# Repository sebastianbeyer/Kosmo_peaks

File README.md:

# Summit is a KOSMO adaption of [Matias Levy's bluepill version](https://github.com/matias-levy/peaks) of [Mutable instrument's Peaks](https://mutable-instruments.net/modules/peaks/)

> **Warning**
> You need the 128k flash version of the bluepill board which might be difficult to obtain. I was lucky with [this](https://www.amazon.com/Teyleten-Robot-Development-STM32F103C8T6-Learning/dp/B08THXZ6XK) item, someone on the LMNC forum was able to get a 128k [here on aliexpress](https://www.aliexpress.us/item/3256801435312142.html?spm=a2g0o.order_list.0.0.4e301802nbwQXK&gatewayAdapt=glo2usa&_randl_shipto=US), but there is no guarantee!

## Gerbers
Can be found in the [latest release](https://github.com/sebastianbeyer/Kosmo_peaks/releases/latest)

## Firmwares
There's the option to flash one of two firmwares that where ported. The original Mutable Instruments one is in the firmware/peaks directory. The [Mutated Mutables Dead Man's Catch](https://github.com/timchurches/Mutated-Mutables/tree/master/peaks) is in the firmware/peaks2. The later adds a lot of functionality to the module, although the UI becomes a bit confusing. <br>
Compiled binaries and HEX files are provided for both under firmware/build.

## Changes
* Added a driver for the PWM DAC running at **14 bit depth, 48Khz sampling rate.** (File in firmware/peaks/drivers/pwm_dac.h)
* Activated the clock for the TIM4 in firmware/peaks/drivers/system.cc
* **Bypassed the bootloader:** This was done as to simplify the code, it does not interfere with the calibration functionality of the module.
* Redesigned the output portion of the hardware to accommodate to the PWM levels.

## Flashing and development
To make it easier I have left binaries and .HEX files in firmware/build, this can be flashed directly to the bluepill using [STM32CubeProgrammer](https://www.st.com/en/development-tools/stm32cubeprog.html). <br>
Another option is to install the [mutable-dev-environment](https://github.com/pichenettes/mutable-dev-environment) and replace the peaks folder with the one inside /firmware, then executing

    make -f peaks/makefile upload_serial

We use this command because the bootloader is bypassed.

## Thanks
I want to thank Emilie Gillet for open-sourcing her work which is a constant inspiration for many musicians and makers, and encourage everyone interested in this project to checkout the [Mutable instrument's Forum](https://forum.mutable-instruments.net/) in which Emilie is a very active member.

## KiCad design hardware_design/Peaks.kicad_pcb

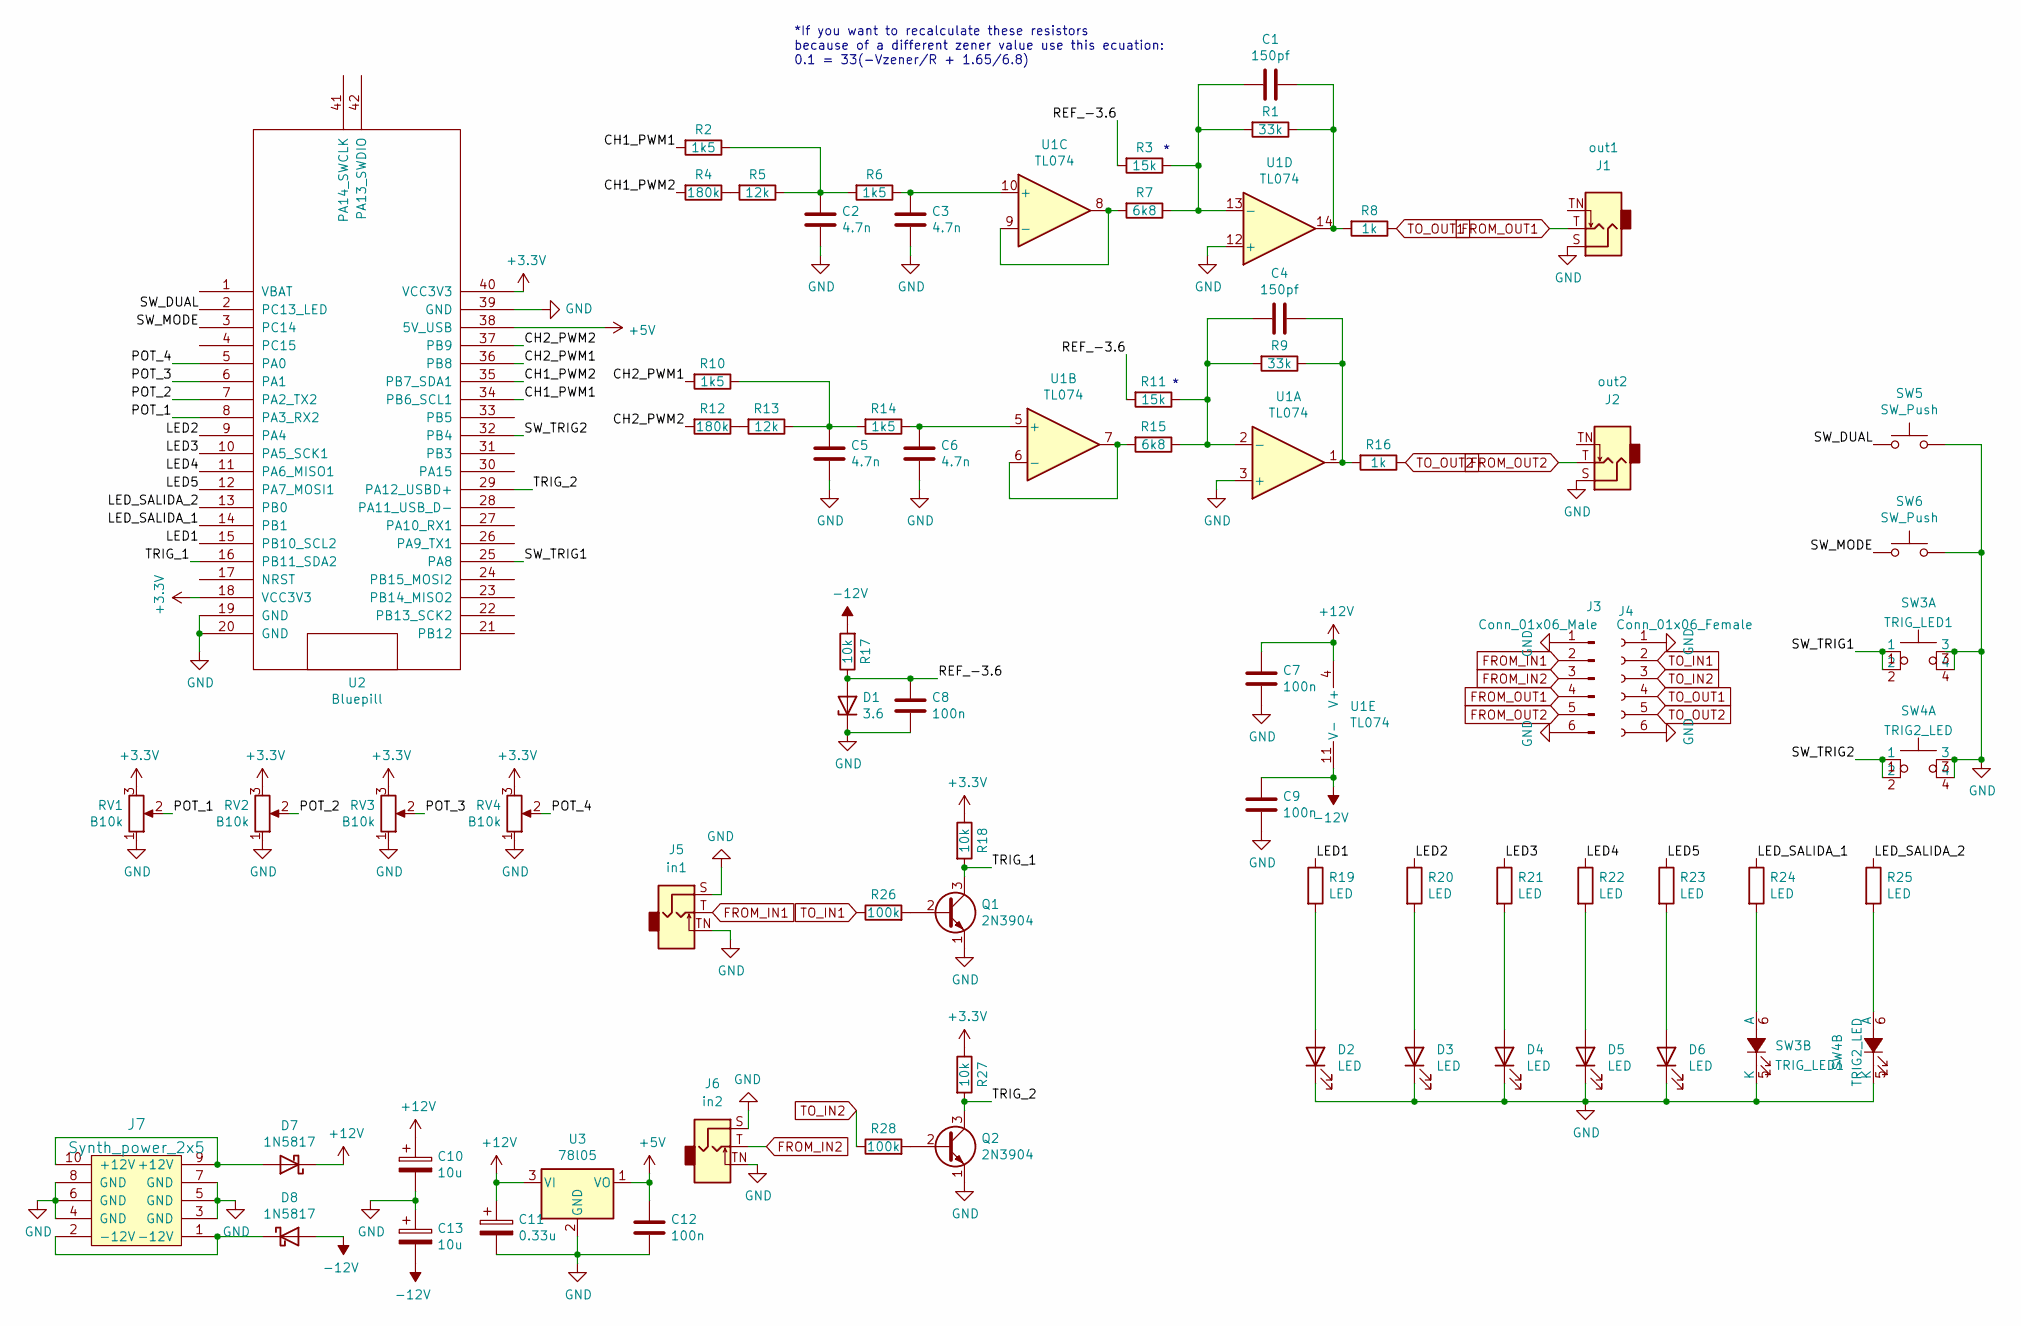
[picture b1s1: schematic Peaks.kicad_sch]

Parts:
C1, C4: 150pf; C_Disc_D3.0mm_W1.6mm_P2.50mm
C2, C3, C5, C6: 4.7n; C_Disc_D3.0mm_W1.6mm_P2.50mm
C7, C8, C9, C12: 100n; C_Disc_D3.0mm_W1.6mm_P2.50mm
C10, C13: 10u; CP_Radial_horizontalflat_D5mm_P2.50mm_H10mm_south
C11: 0.33u; CP_Radial_horizontalflat_D5mm_P2.50mm_H10mm_south
D1: 3.6; D_DO-35_SOD27_P7.62mm_Horizontal
D2, D3, D4, D5, D6: LED; LED_D3.0mm_FlatTop
D7, D8: 1N5817; D_DO-41_SOD81_P10.16mm_Horizontal
J1: out1; Jack_6.35mm_PJ_629HAN_slots
J2: out2; Jack_6.35mm_PJ_629HAN_slots
J3: Conn_01x06_Male; PinHeader_1x06_P2.54mm_Vertical
J4: Conn_01x06_Female; PinSocket_1x06_P2.54mm_Vertical
J5: in1; Jack_6.35mm_PJ_629HAN_slots
J6: in2; Jack_6.35mm_PJ_629HAN_slots
J7: Synth_power_2x5; Power_Header
Q1, Q2: 2N3904; TO-92_Inline_Wide
R1, R9: 33k; R_Axial_DIN0207_L6.3mm_D2.5mm_P10.16mm_Horizontal
R2, R6, R10, R14: 1k5; R_Axial_DIN0207_L6.3mm_D2.5mm_P10.16mm_Horizontal
R3, R11: 15k; R_Axial_DIN0207_L6.3mm_D2.5mm_P10.16mm_Horizontal
R4, R12: 180k; R_Axial_DIN0207_L6.3mm_D2.5mm_P10.16mm_Horizontal
R5, R13: 12k; R_Axial_DIN0207_L6.3mm_D2.5mm_P10.16mm_Horizontal
R7, R15: 6k8; R_Axial_DIN0207_L6.3mm_D2.5mm_P10.16mm_Horizontal
R8, R16: 1k; R_Axial_DIN0207_L6.3mm_D2.5mm_P10.16mm_Horizontal
R17: 10k; R_Axial_DIN0207_L6.3mm_D2.5mm_P10.16mm_Horizontal
R18, R27: 10k; R_Axial_DIN0207_L6.3mm_D2.5mm_P2.54mm_Vertical
R19, R20, R21, R22, R23, R24, R25: LED; R_Axial_DIN0207_L6.3mm_D2.5mm_P2.54mm_Vertical
R26, R28: 100k; R_Axial_DIN0207_L6.3mm_D2.5mm_P2.54mm_Vertical
RV1, RV2, RV3, RV4: B10k; Potentiometer_Alpha_RD901F-40-00D_Single_Vertical_centered
SW3: TRIG_LED1; HIGHLY_PB6149L
SW4: TRIG2_LED; HIGHLY_PB6149L
SW5, SW6: SW_Push; SW_PUSH_6mm_H13mm
U1: TL074; DIP-14_W7.62mm_Socket_LongPads
U2: Bluepill; BluePill_STM32F103C
U3: 78l05; TO-220-3_Horizontal_TabDown

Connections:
+3V3: R18.1, R27.1, RV1.3, RV2.3, RV3.3, RV4.3, U2.18 (VCC3V3), U2.40 (VCC3V3)
+5V: C12.1, U2.38 (5V_USB), U3.1 (VO)
+12V: C7.1, C10.1, C11.1, D7.1 (K), U1.4 (V+), U3.3 (VI)
-12V: C9.1, C13.2, D8.2 (A), R17.2, U1.11 (V-)
/CH1_PWM1: R2.2, U2.34 (PB6_SCL1)
/CH1_PWM2: R4.2, U2.35 (PB7_SDA1)
/CH2_PWM1: R10.2, U2.36 (PB8)
/CH2_PWM2: R12.2, U2.37 (PB9)
/LED1: R19.1, U2.15 (PB10_SCL2)
/LED2: R20.1, U2.9 (PA4)
/LED3: R21.1, U2.10 (PA5_SCK1)
/LED4: R22.1, U2.11 (PA6_MISO1)
/LED5: R23.1, U2.12 (PA7_MOSI1)
/LED_SALIDA_1: R24.1, U2.14 (PB1)
/LED_SALIDA_2: R25.1, U2.13 (PB0)
/POT_1: RV1.2, U2.8 (PA3_RX2)
/POT_2: RV2.2, U2.7 (PA2_TX2)
/POT_3: RV3.2, U2.6 (PA1)
/POT_4: RV4.2, U2.5 (PA0)
/REF_-3.6: C8.1, D1.2 (A), R3.2, R11.2, R17.1
/SW_DUAL: SW5.1, U2.2 (PC13_LED)
/SW_MODE: SW6.1, U2.3 (PC14)
/SW_TRIG1: SW3.1, SW3.2, U2.25 (PA8)
/SW_TRIG2: SW4.1, SW4.2, U2.32 (PB4)
/TRIG_1: Q1.3 (C), R18.2, U2.16 (PB11_SDA2)
/TRIG_2: Q2.3 (C), R27.2, U2.29 (PA12_USBD+)
FROM_IN1: J3.2, J5.T
FROM_IN2: J3.3, J6.T
FROM_OUT1: J1.T, J3.4
FROM_OUT2: J2.T, J3.5
GND: C2.2, C3.2, C5.2, C6.2, C7.2, C8.2, C9.2, C10.2, C11.2, C12.2, C13.1, D1.1 (K), D2.1 (K), D3.1 (K), D4.1 (K), D5.1 (K), D6.1 (K), J1.S, J2.S, J3.1, J3.6, J4.1, J4.6, J5.S, J5.TN, J6.S, J6.TN, J7.3 (GND), J7.4 (GND), J7.5 (GND), J7.6 (GND), J7.7 (GND), J7.8 (GND), Q1.1 (E), Q2.1 (E), RV1.1, RV2.1, RV3.1, RV4.1, SW3.3, SW3.4, SW3.5 (K), SW4.3, SW4.4, SW4.5 (K), SW5.2, SW6.2, U1.3 (+), U1.12 (+), U2.19 (GND), U2.20 (GND), U2.39 (GND), U3.2 (GND)
unnamed: C1.1, R1.2, R3.1, R7.1, U1.13 (-)
unnamed: C1.2, R1.1, R8.2, U1.14
unnamed: C2.1, R2.1, R5.1, R6.2
unnamed: C3.1, R6.1, U1.10 (+)
unnamed: C4.1, R9.2, R11.1, R15.1, U1.2 (-)
unnamed: C4.2, R9.1, R16.2, U1.1
unnamed: C5.1, R10.1, R13.1, R14.2
unnamed: C6.1, R14.1, U1.5 (+)
unnamed: D2.2 (A), R19.2
unnamed: D3.2 (A), R20.2
unnamed: D4.2 (A), R21.2
unnamed: D5.2 (A), R22.2
unnamed: D6.2 (A), R23.2
unnamed: D7.2 (A), J7.9 (+12V), J7.10 (+12V)
unnamed: D8.1 (K), J7.1 (-12V), J7.2 (-12V)
unnamed: Q1.2 (B), R26.2
unnamed: Q2.2 (B), R28.2
unnamed: R4.1, R5.2
unnamed: R7.2, U1.8, U1.9 (-)
unnamed: R12.1, R13.2
unnamed: R15.2, U1.6 (-), U1.7
unnamed: R24.2, SW3.6 (A)
unnamed: R25.2, SW4.6 (A)
TO_IN1: J4.2, R26.1
TO_IN2: J4.3, R28.1
TO_OUT1: J4.4, R8.1
TO_OUT2: J4.5, R16.1

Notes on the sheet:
*If you want to recalculate these resistors because of a different zener value use this ecuation: 0.1 = 33(-Vzener/R + 1.65/6.8)

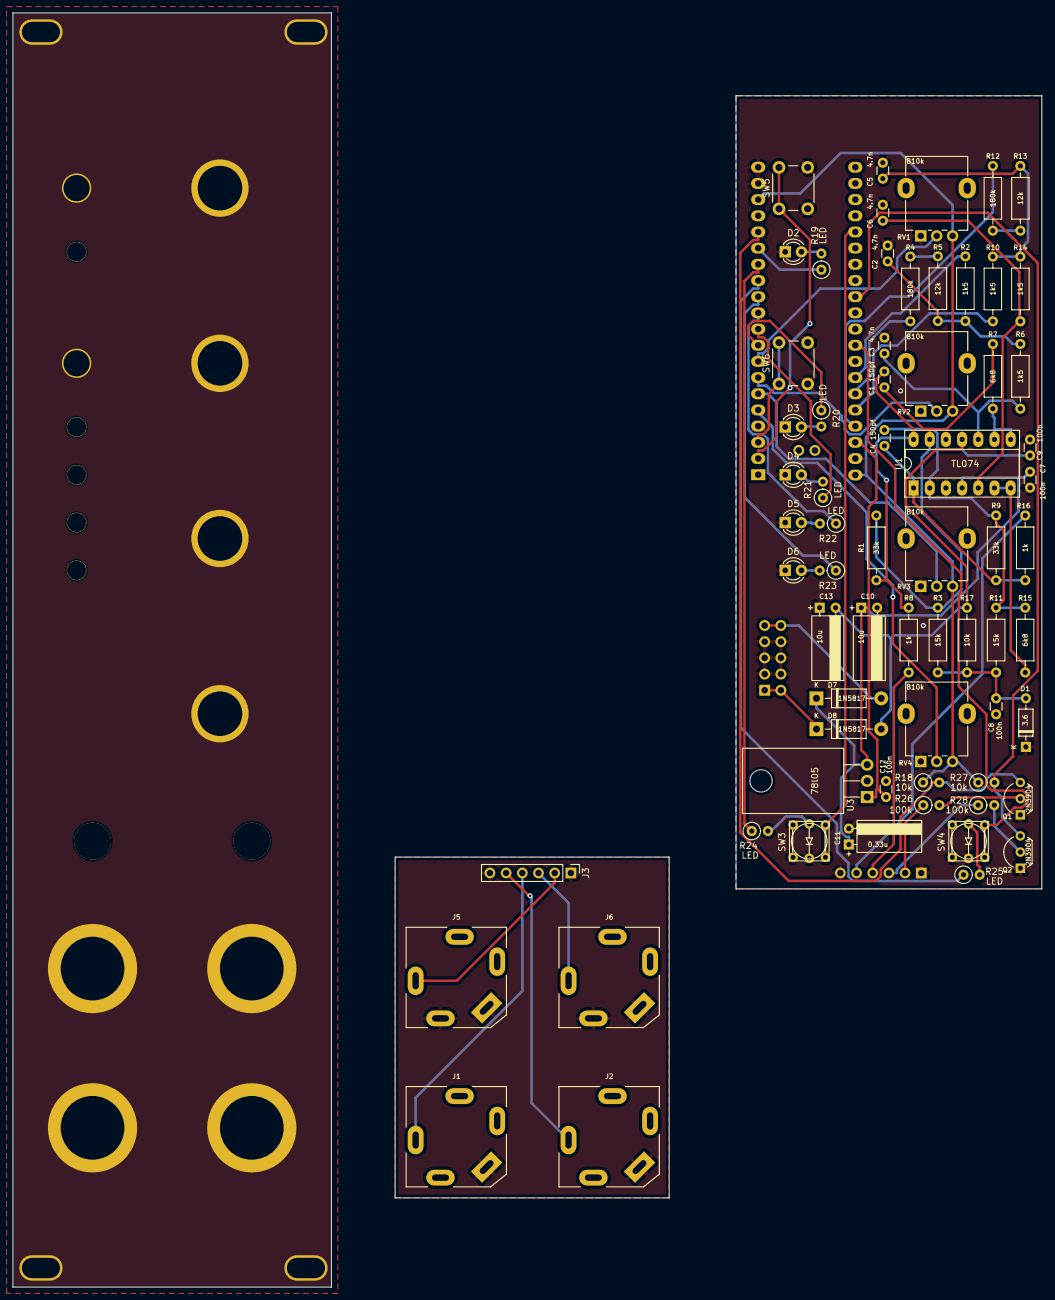
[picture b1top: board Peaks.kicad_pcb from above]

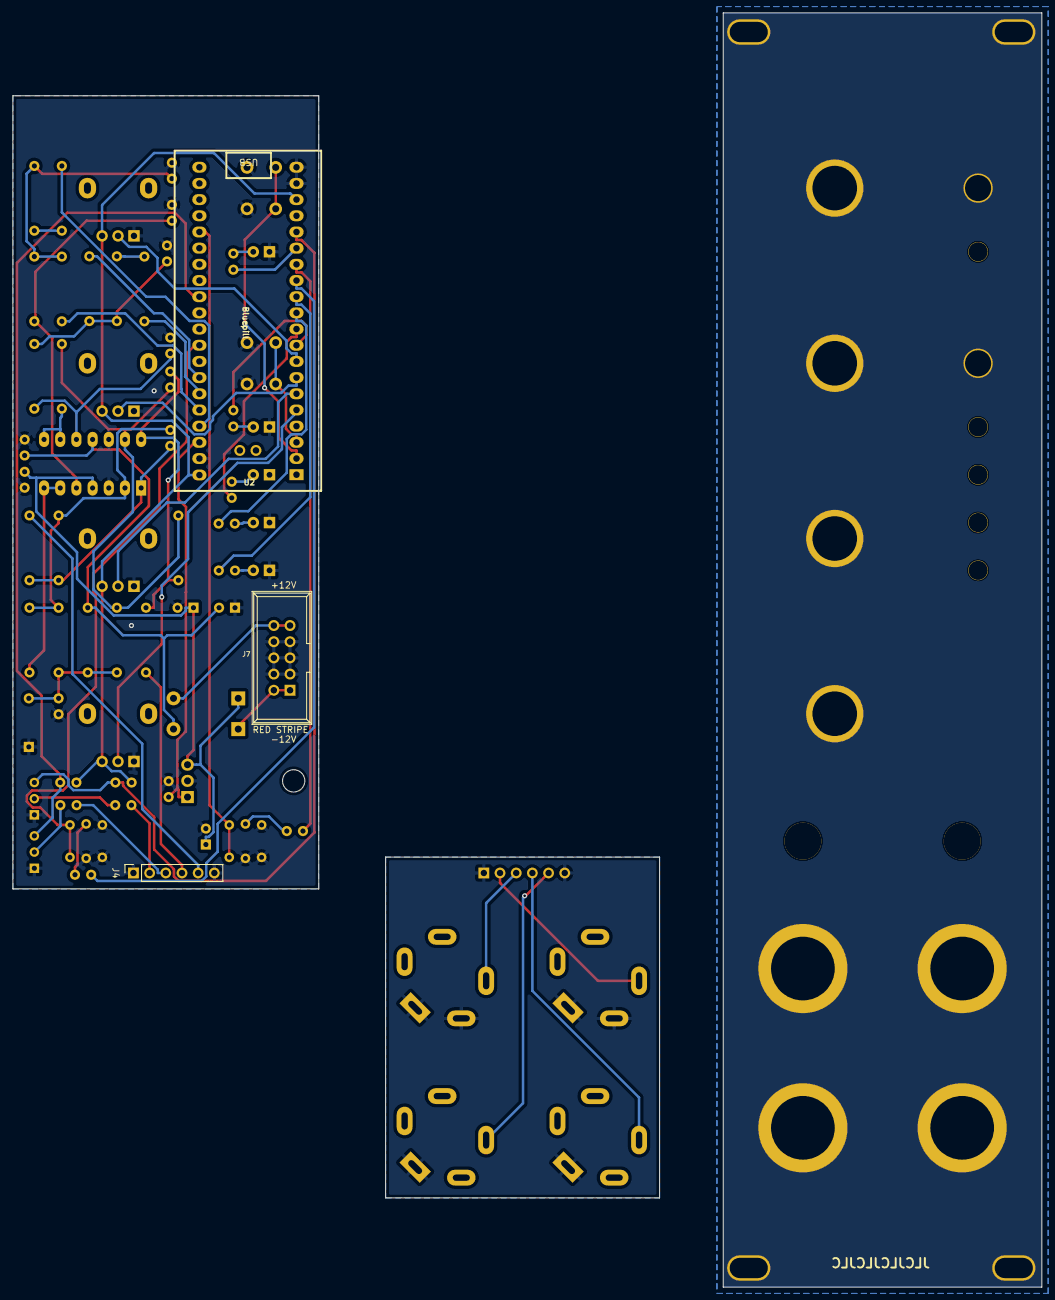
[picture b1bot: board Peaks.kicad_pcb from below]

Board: 2 copper layers, 161.5 x 200.0 mm, 71 parts (3 on the bottom side), 58 nets.

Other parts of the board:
H25, H25#2: led; Kosmo_HIGHLY_PB6149L

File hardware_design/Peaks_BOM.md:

# Peaks.kicad_sch BOM

Tue 22 Nov 2022 12:02:50 CET

Generated from schematic by Eeschema 6.0.8-f2edbf62ab~116~ubuntu22.04.1

**Component Count:** 69

| Refs | Qty | Component | Description | Vendor | SKU |
| ----- | --- | ---- | ----------- | ---- | ---- |
| C1, C4 | 2 | 150pf | Unpolarized capacitor |  |  |
| C2, C3, C5, C6 | 4 | 4.7n | Unpolarized capacitor |  |  |
| C7, C8, C9, C12 | 4 | 100n | Unpolarized capacitor |  |  |
| C10, C13 | 2 | 10u |  |  |  |
| C11 | 1 | 0.33u |  |  |  |
| D1 | 1 | 3.6 | Zener diode |  |  |
| D2, D3, D4, D5, D6 | 5 | LED | 3 mm Light emitting diode |  |  |
| D7, D8 | 2 | 1N5817 | 20V 1A Schottky Barrier Rectifier Diode, DO-41 |  |  |
| J1 | 1 | out1 | Audio Jack, 2 Poles (Mono / TS), Switched T Pole (Normalling) |  |  |
| J2 | 1 | out2 | Audio Jack, 2 Poles (Mono / TS), Switched T Pole (Normalling) |  |  |
| J3 | 1 | Conn_01x06_Male | Generic connector, single row, 01x06, script generated (kicad-library-utils/schlib/autogen/connector/) |  |  |
| J4 | 1 | Conn_01x06_Female | Generic connector, single row, 01x06, script generated (kicad-library-utils/schlib/autogen/connector/) |  |  |
| J5 | 1 | in1 | Audio Jack, 2 Poles (Mono / TS), Switched T Pole (Normalling) |  |  |
| J6 | 1 | in2 | Audio Jack, 2 Poles (Mono / TS), Switched T Pole (Normalling) |  |  |
| J7 | 1 | Synth_power_2x5 | Pin header 2.54 mm 2x5 | Tayda | A-2939 |
| Q1, Q2 | 2 | 2N3904 | 0.2A Ic, 40V Vce, Small Signal NPN Transistor, TO-92 |  |  |
| R1, R9 | 2 | 33k | Resistor |  |  |
| R2, R6, R10, R14 | 4 | 1k5 | Resistor |  |  |
| R3, R11 | 2 | 15k | Resistor |  |  |
| R4, R12 | 2 | 180k | Resistor |  |  |
| R5, R13 | 2 | 12k | Resistor |  |  |
| R7, R15 | 2 | 6k8 | Resistor |  |  |
| R8, R16 | 2 | 1k | Resistor |  |  |
| R17 | 1 | 10k | Resistor |  |  |
| R18, R27 | 2 | 10k | Resistor |  |  |
| R19, R20, R21, R22, R23, R24, R25 | 7 | LED | Resistor |  |  |
| R26, R28 | 2 | 100k | Resistor |  |  |
| RV1, RV2, RV3, RV4 | 4 | B10k |  |  |  |
| SW3 | 1 | TRIG_LED1 |  |  | HIGHLY_PB6149L |
| SW4 | 1 | TRIG2_LED |  |  | HIGHLY_PB6149L |
| SW5, SW6 | 2 | SW_Push | Push button switch, generic, two pins |  |  |
| U1 | 1 | TL074 | Quad Low-Noise JFET-Input Operational Amplifiers, DIP-14/SOIC-14 |  |  |
| U2 | 1 | Bluepill |  |  |  |
| U3 | 1 | 78l05 | Positive 100mA 30V Linear Regulator, Fixed Output 5V, TO-92 |  |  |

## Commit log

2022-11-15 update my KOSMO adaption
2022-11-15 add link to release in readme
2022-11-22 add bom
